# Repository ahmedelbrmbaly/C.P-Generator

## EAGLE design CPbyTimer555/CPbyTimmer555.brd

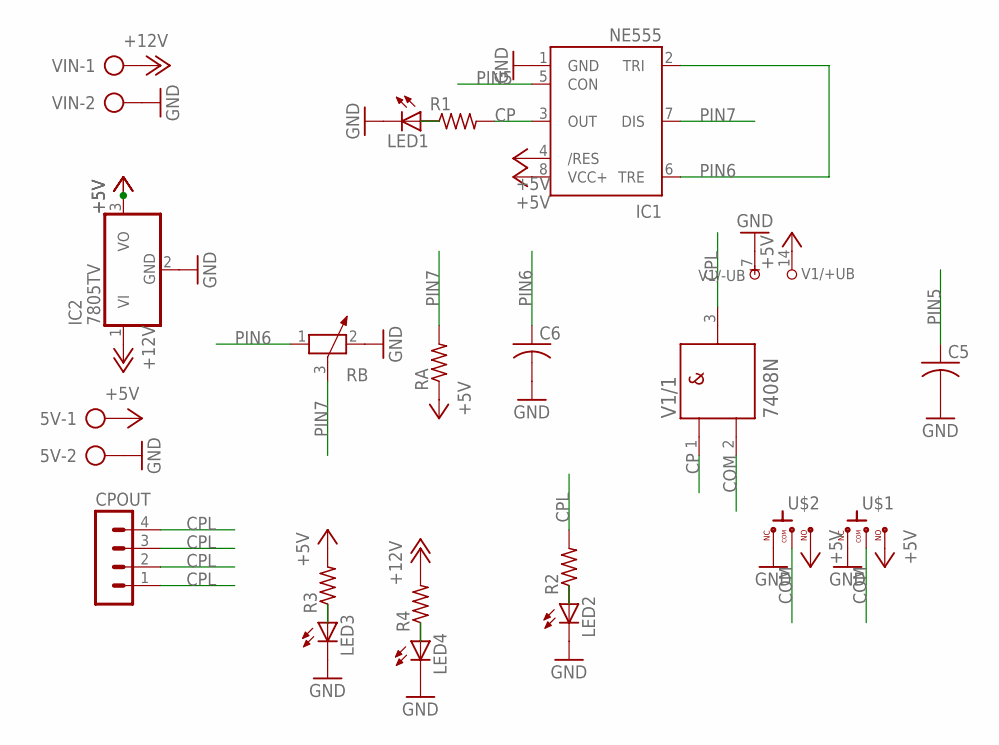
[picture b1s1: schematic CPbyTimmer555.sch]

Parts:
5V: AK500/2-H
C5, C6: C-US025-025X050; C025-025X050
CPOUT: MA04-1
IC1: NE555; DIL-08
IC2: 7805TV; TO220V
LED1, LED2, LED3, LED4: LED_ELD260; LED_LD260
R1, R2, R3, R4: R-US_0204/5; 0204/5
RA: R-US_0204/5; 0204/5
RB: POTENTIOMETER_PT-10; PT-10
U$1, U$2: -SWITCH; CON3
V1: 7408N; DIL14
VIN: AK500/2-H

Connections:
+5V: 5V.1, IC1.4 (/RES), IC1.8 (VCC+), IC2.3 (VO), R3.2, RA.1, U$1.P$3 (3), U$2.P$3 (3), V1.14 (+UB)
+12V: IC2.1 (VI), R4.2, VIN.1
COM: U$1.P$2 (2), U$2.P$2 (2), V1.2 (B)
CP: IC1.3 (OUT), R1.2, V1.1 (A)
CPL: CPOUT.1, CPOUT.2, CPOUT.3, CPOUT.4, R2.2, V1.3 (Y)
GND: 5V.2, C5.2, C6.2, IC1.1 (GND), IC2.2 (GND), LED1.K (C), LED2.K (C), LED3.K (C), LED4.K (C), RB.2, U$1.P$1 (1), U$2.P$1 (1), V1.7 (-UB), VIN.2
unnamed: LED1.A, R1.1
unnamed: LED2.A, R2.1
unnamed: LED3.A, R3.1
unnamed: LED4.A, R4.1
PIN5: C5.1, IC1.5 (CON)
PIN6: C6.1, IC1.2 (TRI), IC1.6 (TRE), RB.1
PIN7: IC1.7 (DIS), RA.2, RB.3

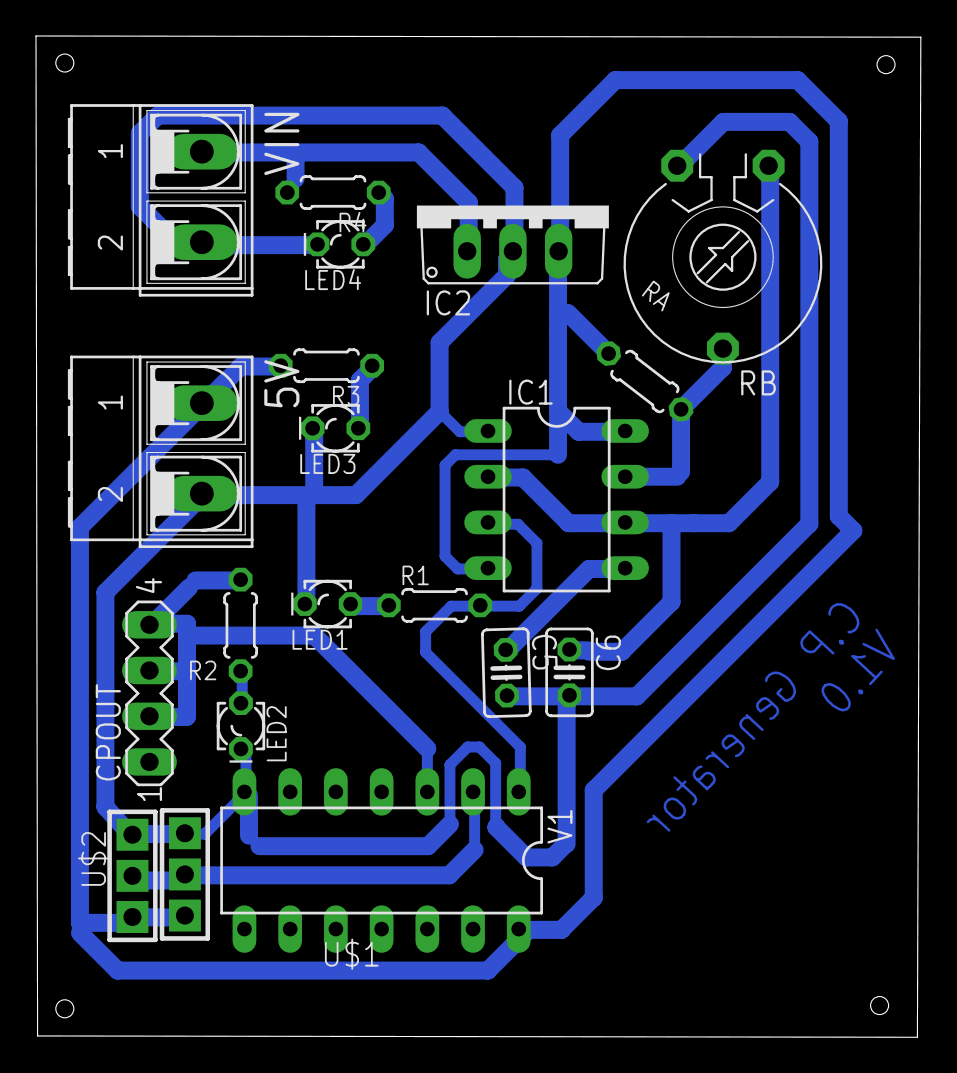
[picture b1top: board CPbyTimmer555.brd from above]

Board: 2 copper layers, 49.2 x 55.6 mm, 20 parts (0 on the bottom side), 13 nets.
